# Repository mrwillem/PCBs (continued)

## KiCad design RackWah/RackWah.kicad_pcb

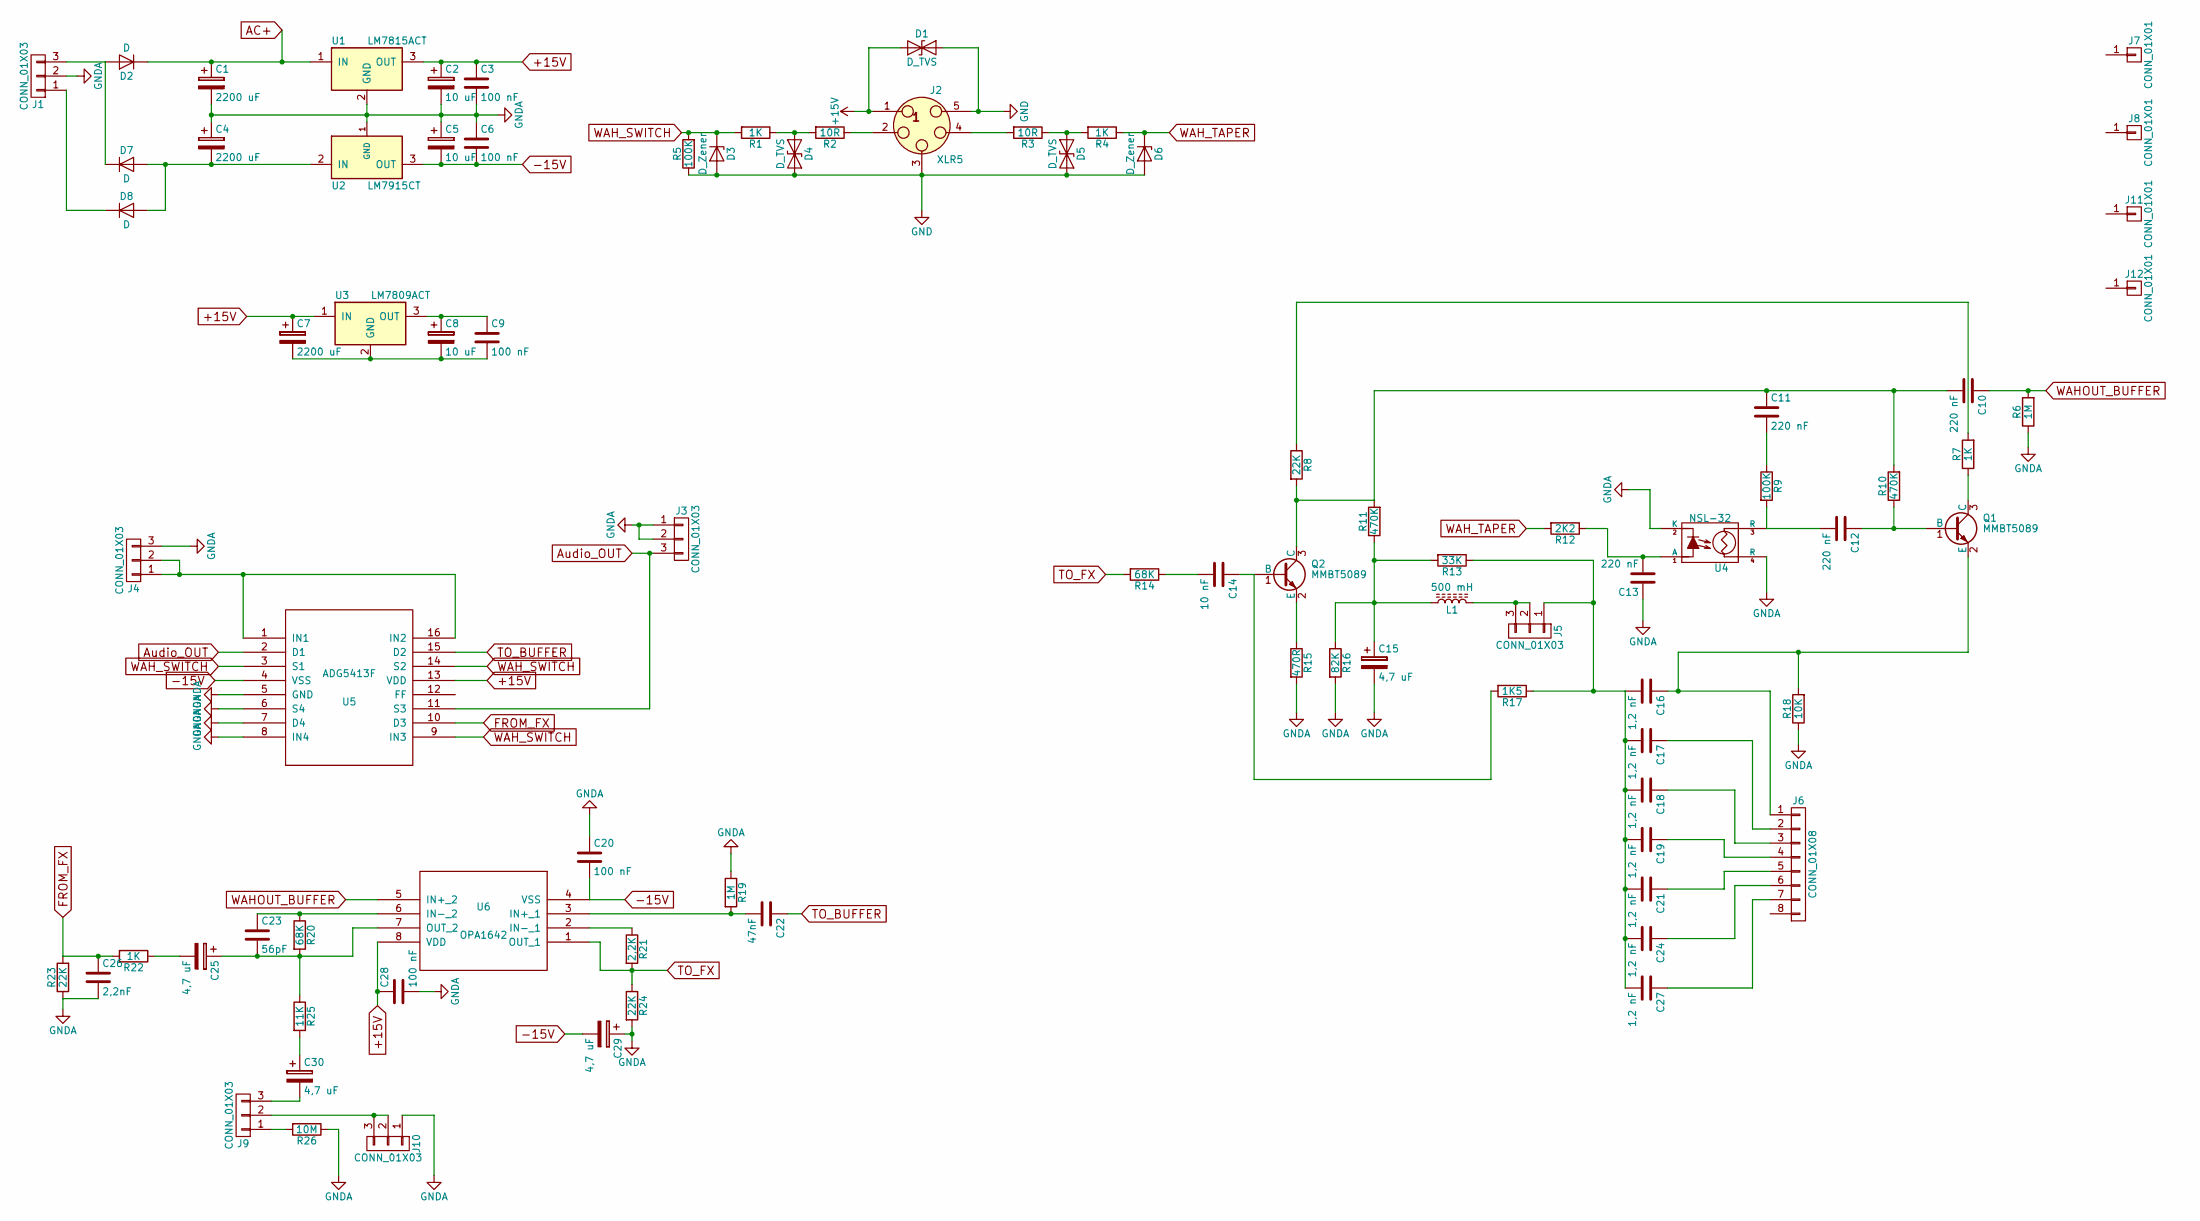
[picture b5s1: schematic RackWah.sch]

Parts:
C1, C4, C7: 2200 uF; CP_Elec_10x10.5
C2, C5, C8: 10 uF; CP_Elec_5x5.8
C3, C6, C9, C20, C28: 100 nF; R_0805_HandSolder
C10, C11, C12: 220 nF; Capacitor-Wima-SMD2824-63v-L7,2
C13: 220 nF; R_0805_HandSolder
C14: 10 nF; C_1206_HandSoldering
C15, C29: 4,7 uF; CP_Elec_4x5.8
C16, C17, C18, C19, C21, C24, C27: 1,2 nF; C_Disc_D3.8mm_W2.6mm_P2.50mm
C22: 47nF; C_1812_HandSoldering
C23: 56pF; C_Disc_D6.5mm_W4.0mm_P3.50mm
C25, C30: 4,7 uF; C_Rect_L19.0mm_W11.0mm_P15.00mm_MKS4
C26: 2,2nF; C_1206_HandSoldering
D1, D4, D5: D_TVS; D_SMB
D2, D7, D8: D; D_SMA_Handsoldering
D3, D6: D_Zener; D_SMB
J1, J3, J4, J5, J9, J10: CONN_01X03; Molex_MicroLatch-53253-0370_03x2.00mm_Straight
J2: XLR5; Molex_KK-6410-05_05x2.54mm_Straight
J6: CONN_01X08; Molex_KK-6410-08_08x2.54mm_Straight
J7, J8, J11, J12: CONN_01X01; MountingHole_4.3mm_M4
L1: 500 mH; Choke_Horizontal_RM12.5_DunlopWah
Q1, Q2: MMBT5089; SOT-23
R1, R4, R7, R22: 1K; R_0805_HandSolder
R2, R3: 10R; R_0805_HandSolder
R5, R9: 100K; R_0805_HandSolder
R6, R19: 1M; R_0805_HandSolder
R8, R23, R24: 22K; R_0805_HandSolder
R10, R11: 470K; R_0805_HandSolder
R12: 2K2; R_0805_HandSolder
R13: 33K; R_0805_HandSolder
R14, R20: 68K; R_0805_HandSolder
R15: 470R; R_0805_HandSolder
R16: 82K; R_0805_HandSolder
R17: 1K5; R_0805_HandSolder
R18: 10K; R_0805_HandSolder
R21: 2,2K; R_0805_HandSolder
R25: 11K; R_0805_HandSolder
R26: 10M; R_0805_HandSolder
U1: LM7815ACT; TO-252-3_TabPin2
U2: LM7915CT; TO-252-3_TabPin2
U3: LM7809ACT; TO-252-3_TabPin2
U4: NSL-32; Optoisolator_NSL-32
U5: ADG5413F; TSSOP-16_4.4x5mm_Pitch0.65mm
U6: OPA1642; SOIC-8_3.9x4.9mm_Pitch1.27mm

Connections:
+15V: C2.1, C3.1, C7.1, C28.1, D1.1 (A1), J2.1, U1.3 (OUT), U3.1 (IN), U5.13 (VDD), U6.8 (VDD)
-15V: C5.2, C6.2, C20.2, C29.2, U2.3 (OUT), U5.4 (VSS), U6.4 (VSS)
AC+: C1.1, D2.1 (K), U1.1 (IN)
Audio_OUT: J3.3, U5.2 (D1), U5.11 (S3)
FROM_FX: C26.1, R22.2, R23.2, U5.10 (D3)
GND: D1.2 (A2), D3.2 (A), D4.2 (A2), D5.2 (A2), D6.2 (A), J2.3, J2.5, R5.1
GNDA: C1.2, C2.2, C3.2, C4.1, C5.1, C6.1, C13.1, C15.2, C20.1, C26.2, C28.2, C29.1, J1.2, J3.1, J3.2, J4.3, J10.1, R6.1, R15.2, R16.2, R18.1, R19.1, R23.1, R24.2, R26.1, U1.2 (GND), U2.1 (GND), U4.2 (K), U4.4 (R), U5.5 (GND), U5.6 (S4), U5.7 (D4), U5.8 (IN4)
unnamed: C4.2, D7.2 (A), D8.2 (A), U2.2 (IN)
unnamed: C7.2, C8.2, C9.2, U3.2 (GND)
unnamed: C8.1, C9.1, U3.3 (OUT)
unnamed: C10.2, C11.1, Q2.3 (C), R8.2, R10.2, R11.2
unnamed: C11.2, R9.1
unnamed: C12.1, Q1.1 (B), R10.1
unnamed: C12.2, R9.2, U4.3 (R)
unnamed: C13.2, R12.1, U4.1 (A)
unnamed: C14.1, Q2.1 (B), R17.2
unnamed: C14.2, R14.1
unnamed: C15.1, L1.1, R11.1, R13.2, R16.1
unnamed: C16.1, J6.1, Q1.2 (E), R18.2
unnamed: C16.2, C17.2, C18.2, C19.2, C21.2, C24.2, C27.2, J5.1, R13.1, R17.1
unnamed: C17.1, J6.2
unnamed: C18.1, J6.3
unnamed: C19.1, J6.4
unnamed: C21.1, J6.5
unnamed: C22.2, R19.2, U6.3 (IN+_1)
unnamed: C23.1, R20.1, U6.6 (IN-_2)
unnamed: C23.2, C25.1, R20.2, R25.1, U6.7 (OUT_2)
unnamed: C24.1, J6.6
unnamed: C25.2, R22.1
unnamed: C27.1, J6.7
unnamed: C30.1, R25.2
unnamed: C30.2, J9.3
unnamed: D2.2 (A), D7.1 (K), J1.3
unnamed: D4.1 (A1), R1.1, R2.2
unnamed: D5.1 (A1), R3.1, R4.2
unnamed: D8.1 (K), J1.1
unnamed: J2.2, R2.1
unnamed: J2.4 (P3), R3.2
unnamed: J4.1, J4.2, U5.1 (IN1), U5.16 (IN2)
unnamed: J5.2, J5.3, L1.2
unnamed: J9.1, R26.2
unnamed: J9.2, J10.2, J10.3
unnamed: Q1.3 (C), R7.1
unnamed: Q2.2 (E), R15.1
unnamed: R7.2, R8.1
unnamed: R21.1, U6.2 (IN-_1)
TO_BUFFER: C22.1, U5.15 (D2)
TO_FX: R14.2, R21.2, R24.1, U6.1 (OUT_1)
WAHOUT_BUFFER: C10.1, R6.2, U6.5 (IN+_2)
WAH_SWITCH: D3.1 (K), R1.2, R5.2, U5.3 (S1), U5.9 (IN3), U5.14 (S2)
WAH_TAPER: D6.1 (K), R4.1, R12.2

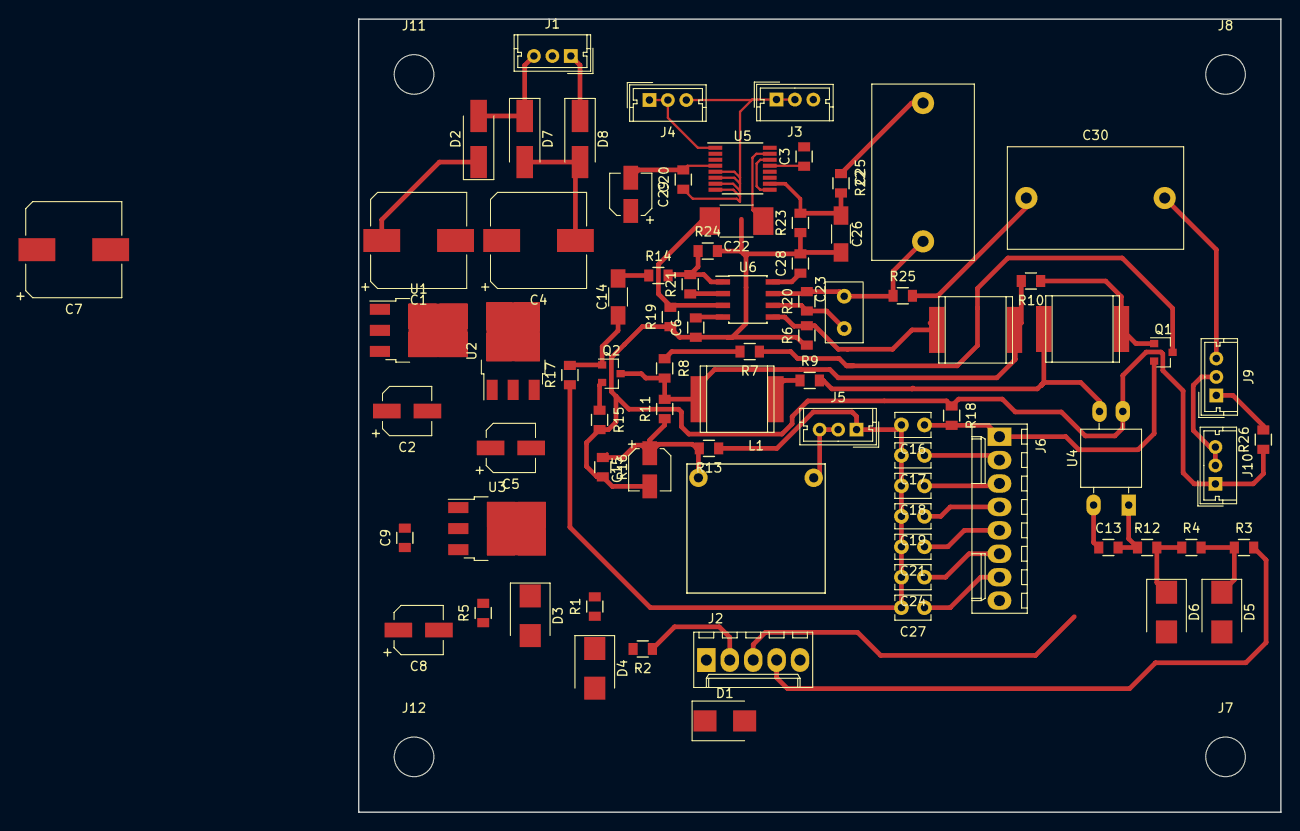
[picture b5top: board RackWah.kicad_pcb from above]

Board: 2 copper layers, 100.0 x 86.0 mm, 85 parts (0 on the bottom side), 51 nets.

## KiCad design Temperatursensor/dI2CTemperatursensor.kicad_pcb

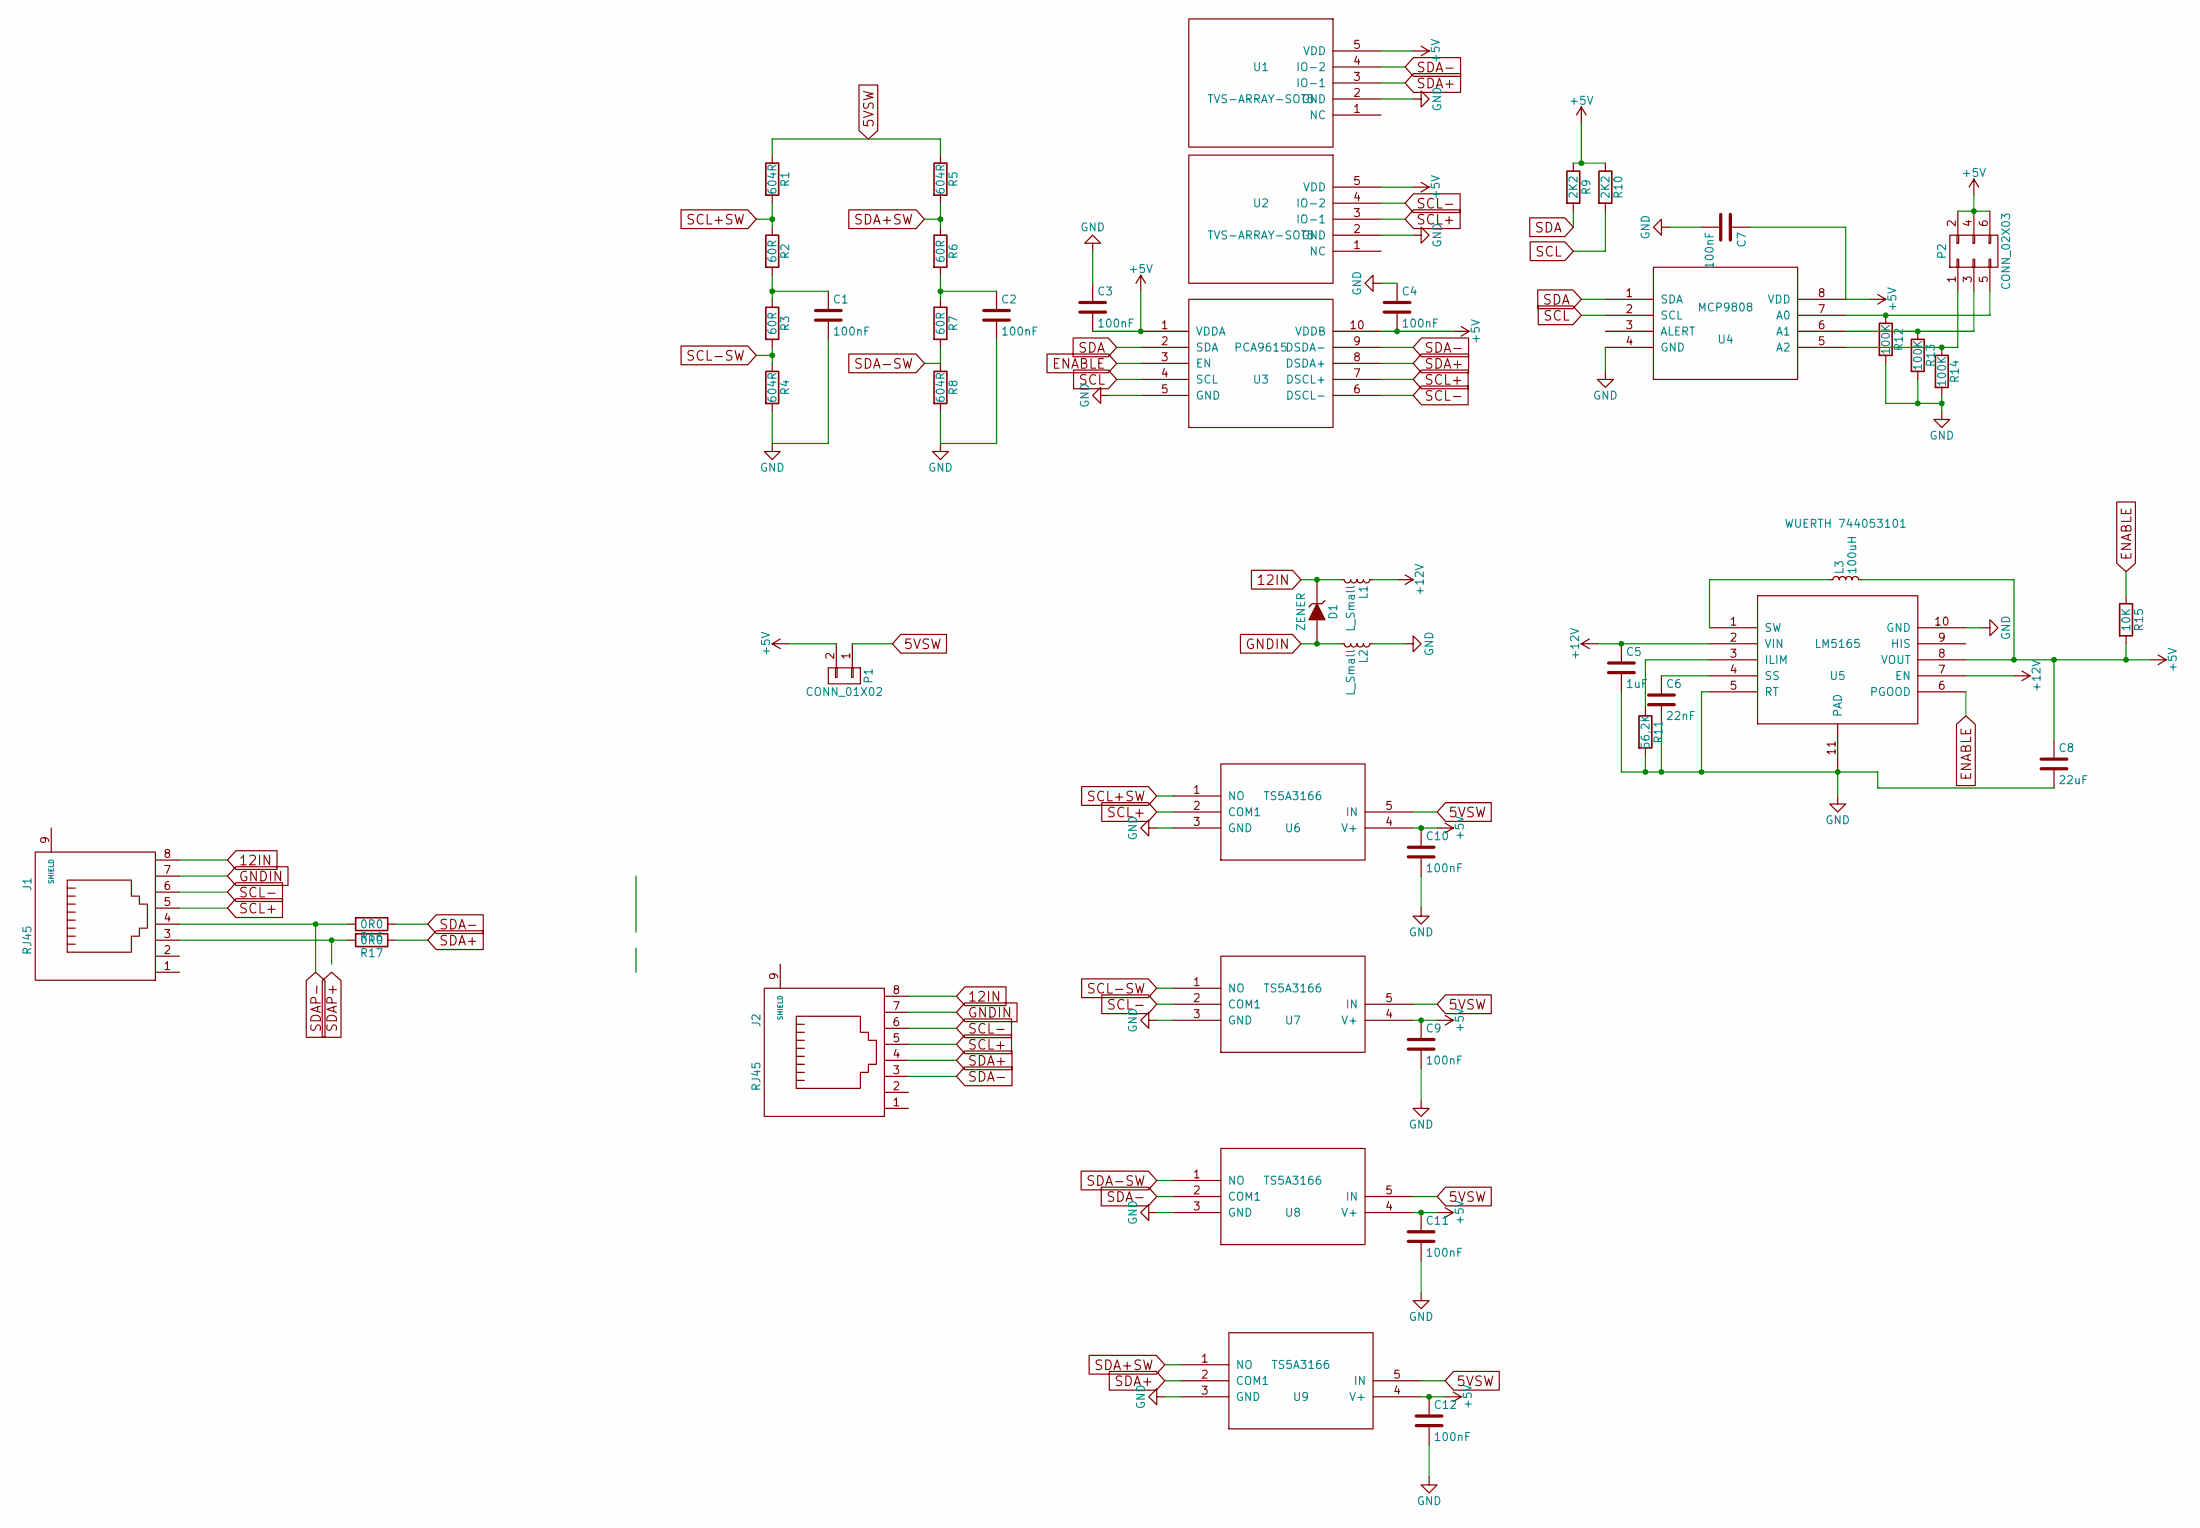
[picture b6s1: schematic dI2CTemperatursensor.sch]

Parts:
C1, C2, C3, C4, C7, C9, C10, C11, C12: 100nF; C_0805
C5: 1uF; C_0805
C6: 22nF; C_0805
C8: 22uF; C_1206
D1: ZENER; SMA_Standard
J1, J2: RJ45; RJ45_8
L1, L2: L_Small; R_0805_HandSoldering
L3: 100uH; Fill_planes_manually_WURTH_ELEKTRONIK_744053221
P1: CONN_01X02; Pin_Header_Straight_1x02
P2: CONN_02X03; Pin_Header_Straight_2x03
R1, R4, R5, R8: 604R; R_0805_HandSoldering
R2, R3, R6, R7: 60R; R_0805_HandSoldering
R9, R10: 2K2; R_0805_HandSoldering
R11: 56,2K; R_0805_HandSoldering
R12, R13, R14: 100K; R_0805_HandSoldering
R15: 10K; R_0805_HandSoldering
R16, R17: 0R0
U1, U2: TVS-ARRAY-SOT5; SOT-23-5
U3: PCA9615; TSSOP-10_3x3mm_Pitch0.5mm
U4: MCP9808; MSOP-8_3x3mm_Pitch0.65mm
U5: LM5165; VSON10_Thermal_Pad
U6, U7, U8, U9: TS5A3166; SC-70-5

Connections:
5VSW: P1.1, R1.1, R5.1, U6.5 (IN), U7.5 (IN), U8.5 (IN), U9.5 (IN)
12IN: D1.1 (K), J1.8, J2.8, L1.2
+5V: C3.2, C4.2, C7.1, C8.1, C9.1, C10.1, C11.1, C12.1, L3.2, P1.2, P2.2, P2.4, P2.6, R9.1, R10.1, R15.2, U1.5 (VDD), U2.5 (VDD), U3.1 (VDDA), U3.10 (VDDB), U4.8 (VDD), U5.8 (VOUT), U6.4 (V+), U7.4 (V+), U8.4 (V+), U9.4 (V+)
+12V: C5.1, L1.1, U5.2 (VIN), U5.7 (EN)
ENABLE: R15.1, U3.3 (EN), U5.6 (PGOOD)
GND: C1.2, C2.2, C3.1, C4.1, C5.2, C6.2, C7.2, C8.2, C9.2, C10.2, C11.2, C12.2, L2.1, R4.2, R8.2, R11.2, R12.2, R13.2, R14.2, U1.2 (GND), U2.2 (GND), U3.5 (GND), U4.4 (GND), U5.5 (RT), U5.10 (GND), U5.11 (PAD), U6.3 (GND), U7.3 (GND), U8.3 (GND), U9.3 (GND)
GNDIN: D1.2 (A), J1.7, J2.7, L2.2
unnamed: C1.1, R2.2, R3.1
unnamed: C2.1, R6.2, R7.1
unnamed: C6.1, U5.4 (SS)
unnamed 12: J1.3, R17.2; also elsewhere on the board
unnamed 13: J1.4, R16.2; also elsewhere on the board
unnamed: L3.1, U5.1 (SW)
unnamed: P2.1, R14.1, U4.5 (A2)
unnamed: P2.3, R13.1, U4.6 (A1)
unnamed: P2.5, R12.1, U4.7 (A0)
unnamed: R11.1, U5.3 (ILIM)
SCL: R10.2, U3.4 (SCL), U4.2 (SCL)
SCL+: J1.5, J2.5, U2.3 (IO-1), U3.7 (DSCL+), U6.2 (COM1)
SCL+SW: R1.2, R2.1, U6.1 (NO)
SCL-: J1.6, J2.6, U2.4 (IO-2), U3.6 (DSCL-), U7.2 (COM1)
SCL-SW: R3.2, R4.1, U7.1 (NO)
SDA: R9.2, U3.2 (SDA), U4.1 (SDA)
SDA+: J2.4, R17.1, U1.3 (IO-1), U3.8 (DSDA+), U9.2 (COM1); also elsewhere on the board
SDA+SW: R5.2, R6.1, U9.1 (NO)
SDA-: J2.3, R16.1, U1.4 (IO-2), U3.9 (DSDA-), U8.2 (COM1); also elsewhere on the board
SDA-SW: R7.2, R8.1, U8.1 (NO)

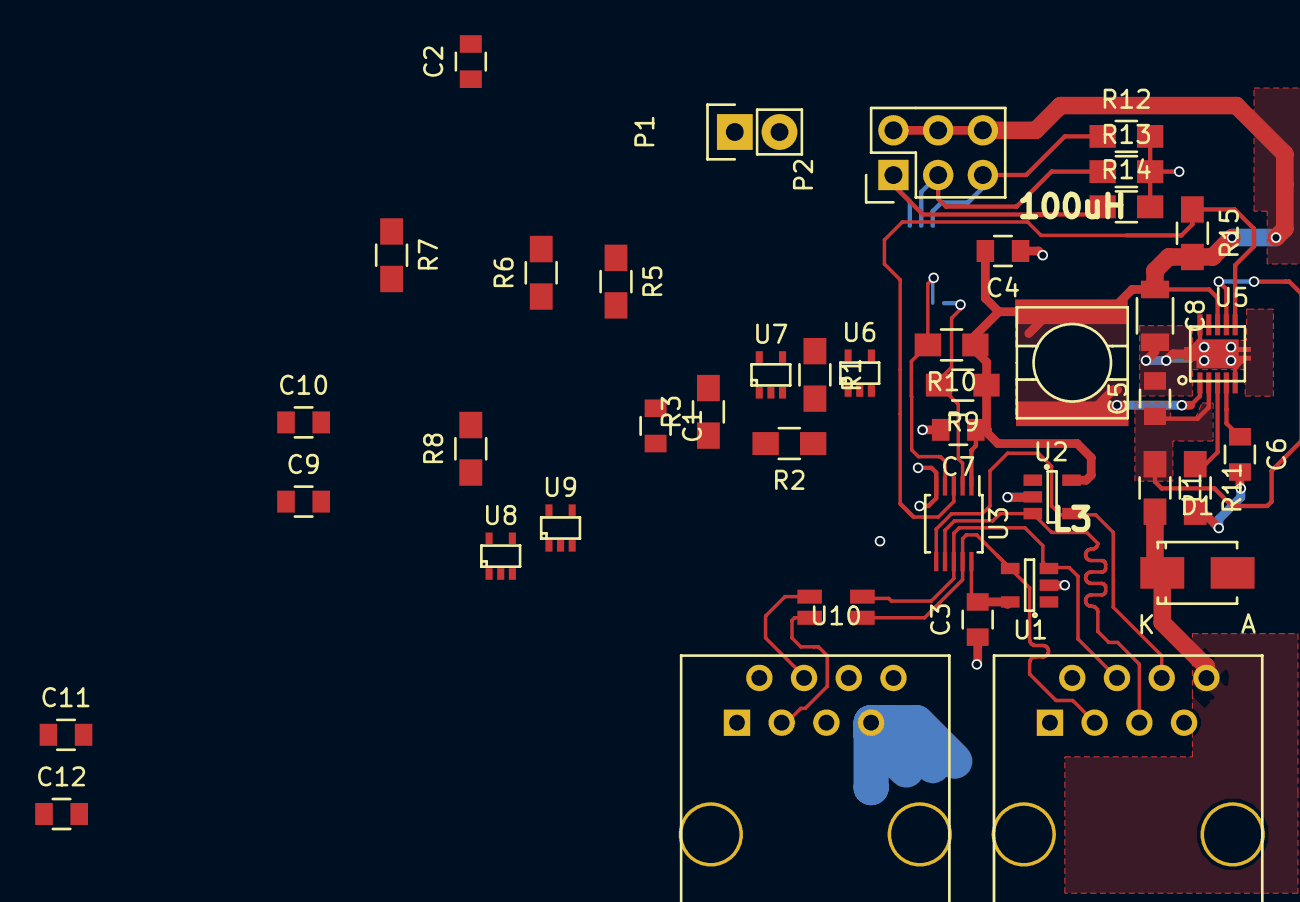
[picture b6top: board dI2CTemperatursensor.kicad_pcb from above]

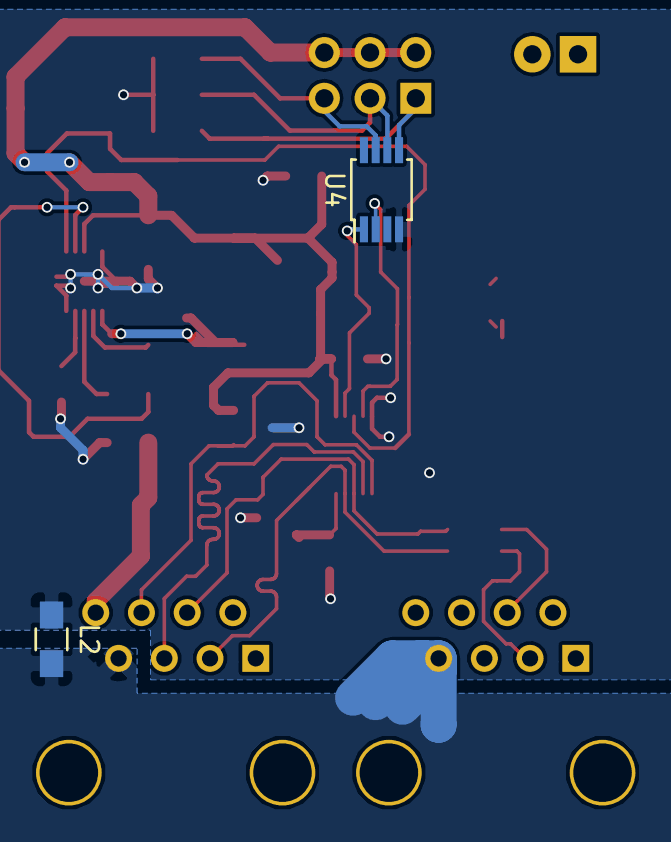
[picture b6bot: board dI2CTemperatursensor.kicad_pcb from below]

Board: 4 copper layers, 44 parts (2 on the bottom side), 27 nets.

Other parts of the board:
U10: USB-CMC-Wuerth; CMC-SMD-Wuerth

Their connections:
unnamed 12: U10.1; also elsewhere on the board
unnamed 13: U10.4; also elsewhere on the board
SDA+: U10.3; also elsewhere on the board
SDA-: U10.2; also elsewhere on the board
